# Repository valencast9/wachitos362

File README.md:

# wachitos362
ECE 362 project repository for Team Wachitos.

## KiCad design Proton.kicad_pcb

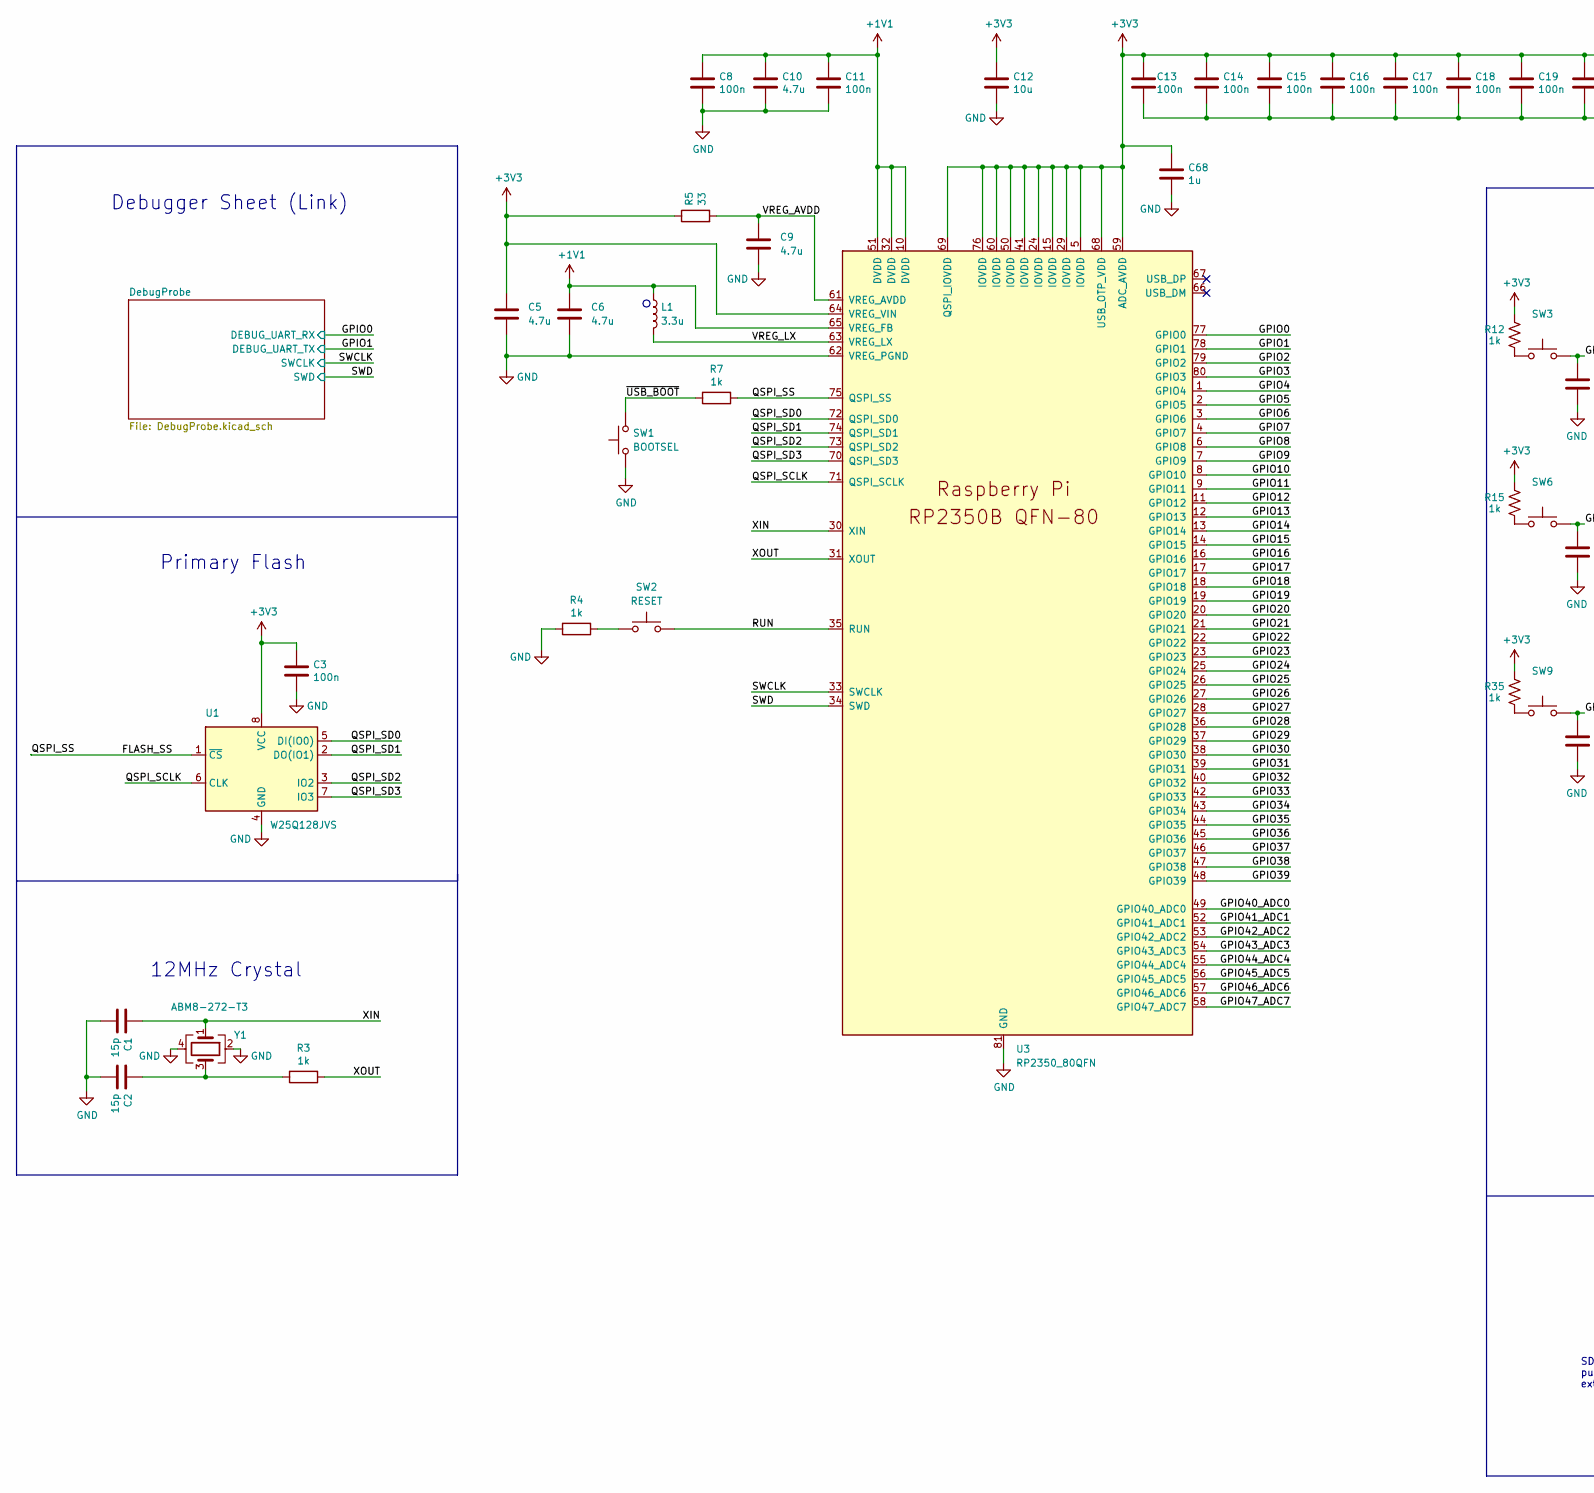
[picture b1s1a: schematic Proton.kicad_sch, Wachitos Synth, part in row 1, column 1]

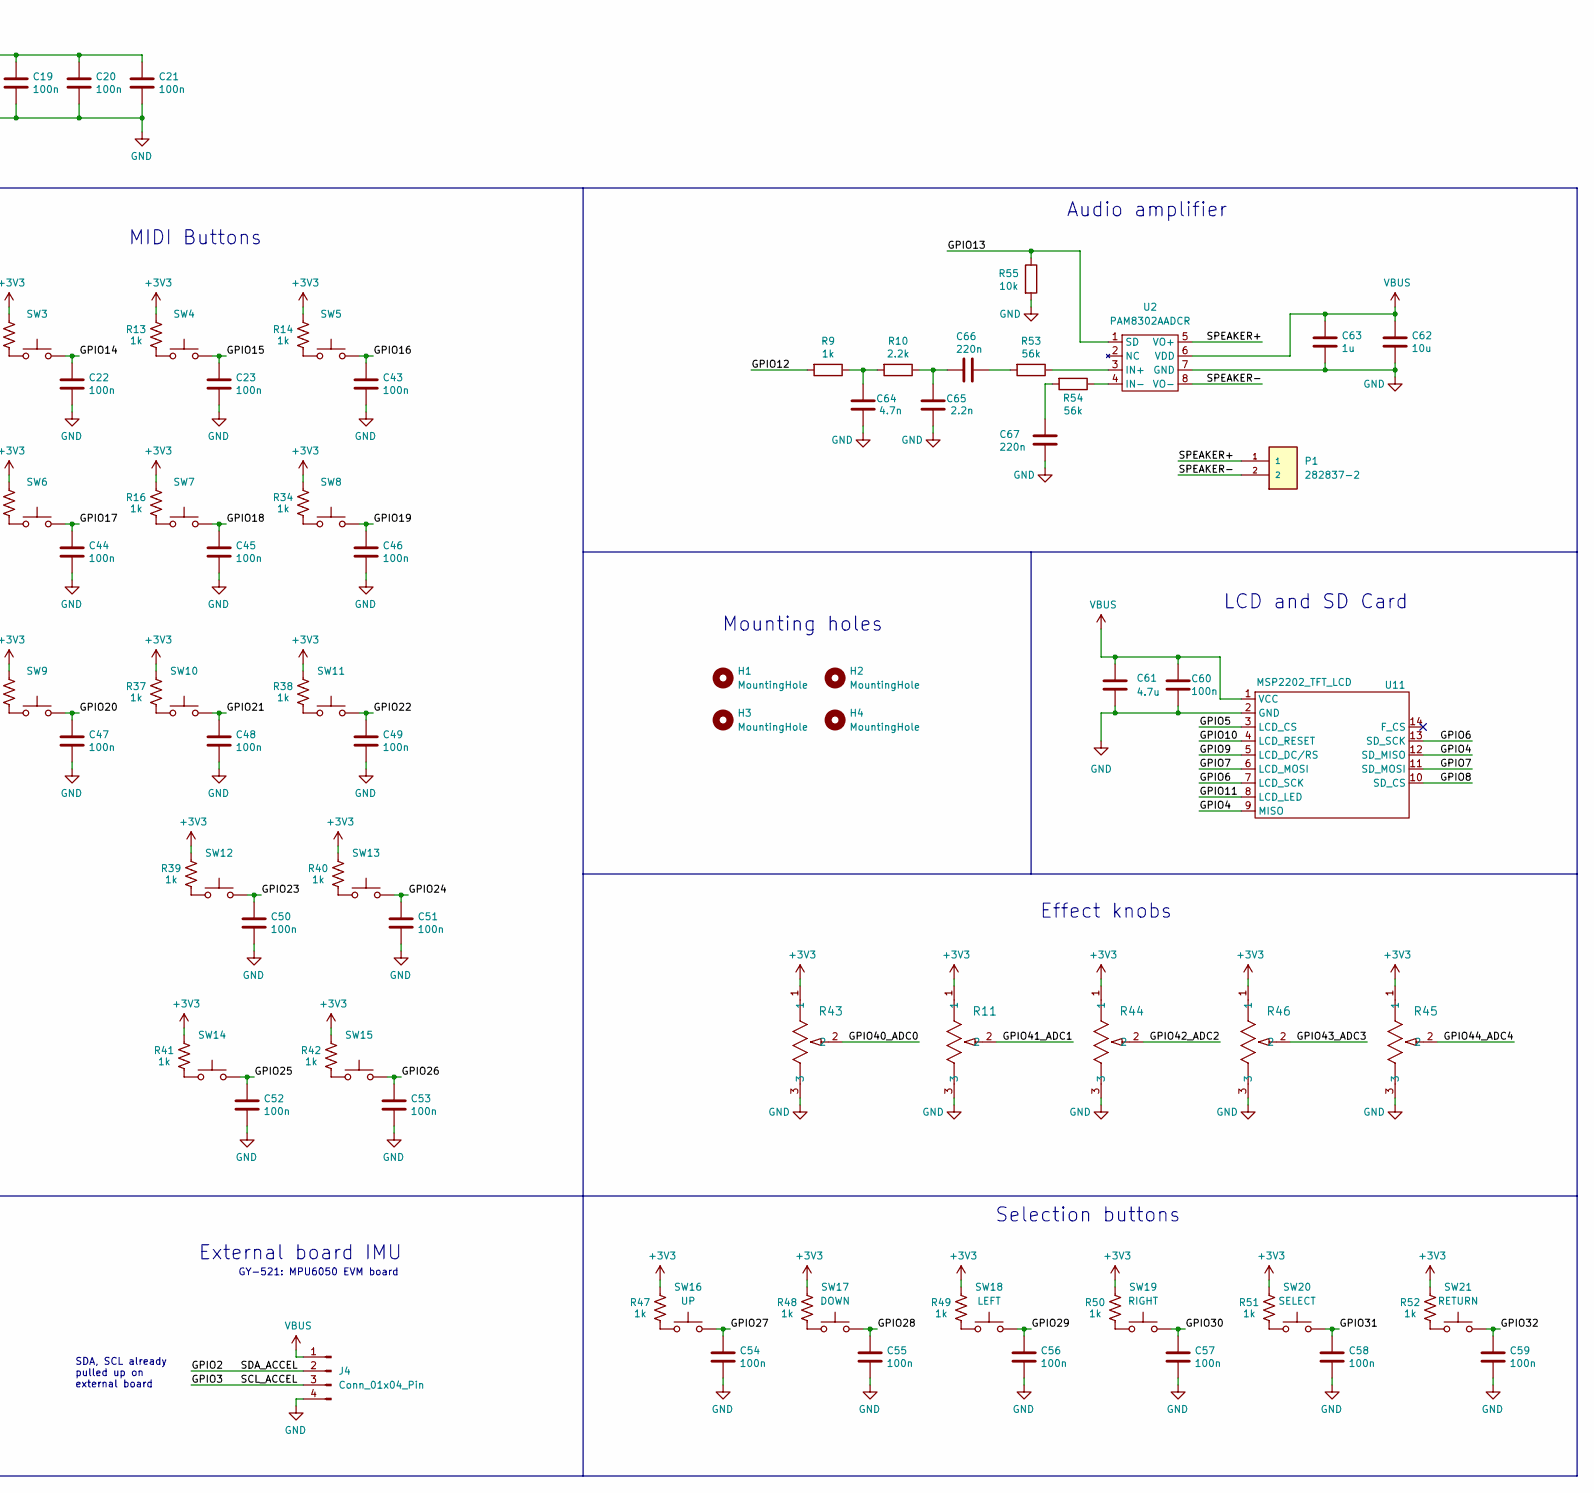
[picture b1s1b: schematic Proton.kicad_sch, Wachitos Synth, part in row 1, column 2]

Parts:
C1, C2: 15p; C_0402_1005Metric; MPN GJM1555C1H150GB01D
C3, C8, C11, C13, C14, C15, C16, C17, C18, C19, C20, C21, C22, C23, C43, C44, C45, C46, C47, C48, C49, C50, C51, C52, C53, C54, C55, C56, C57, C58, C59, C60: 100n; C_0402_1005Metric; MPN CL05B104KP5VPNC
C5, C6, C9, C10, C61: 4.7u; C_0402_1005Metric; MPN CL05A475MP5NRNC
C12, C62: 10u; C_0805_2012Metric; MPN CL21A106KOQNNNE
C63, C68: 1u; C_0402_1005Metric; MPN C1005X6S1C105K050EC
C64: 4.7n; C_0402_1005Metric; MPN CL05B104KP5VPNC
C65: 2.2n; C_0402_1005Metric; MPN CL05B104KP5VPNC
C66, C67: 220n; C_0402_1005Metric; MPN CL05B104KP5VPNC
H1, H2, H3, H4: MountingHole; MountingHole_3.2mm_M3
J4: Conn_01x04_Pin; PinHeader_1x04_P2.54mm_Vertical; MPN PRPC004SACN-RC
L1: 3.3u; L_pol_2016; MPN AOTA-B201610S3R3-101-T
P1: 282837-2; TE_282837-2; PARTREV G3
R3, R4, R7, R9, R12, R13, R14, R15, R16, R34, R35, R37, R38, R39, R40, R41, R42, R47, R48, R49, R50, R51, R52: 1k; R_0402_1005Metric; MPN RC0402JR-071KL
R5: 33; R_0402_1005Metric; MPN RC0402JR-0733RL
R10: 2.2k; R_0402_1005Metric; MPN RC0402JR-071KL
R11, R43, R44, R45, R46: P120PK-Y25BR10K; POT_P120PK-x25_TTE
R53, R54: 56k; R_0402_1005Metric; MPN RC0402JR-071KL
R55: 10k; R_0402_1005Metric; MPN RC0402JR-071KL
SW1: BOOTSEL; SW_SPST_PTS647_Sx38; MPN PTS647SM38SMTR2 LFS
SW2: RESET; SW_SPST_PTS647_Sx38; MPN PTS647SM38SMTR2 LFS
SW3: SW_SPST_PTS647_Sx38; MPN PTS647SM38SMTR2 LFS
SW4, SW5, SW6, SW7, SW8, SW9, SW10, SW11, SW12, SW13, SW14, SW15, SW18: LEFT; SW_SPST_PTS647_Sx38; MPN PTS647SM38SMTR2 LFS
SW16: UP; SW_SPST_PTS647_Sx38; MPN PTS647SM38SMTR2 LFS
SW17: DOWN; SW_SPST_PTS647_Sx38; MPN PTS647SM38SMTR2 LFS
SW19: RIGHT; SW_SPST_PTS647_Sx38; MPN PTS647SM38SMTR2 LFS
SW20: SELECT; SW_SPST_PTS647_Sx38; MPN PTS647SM38SMTR2 LFS
SW21: RETURN; SW_SPST_PTS647_Sx38; MPN PTS647SM38SMTR2 LFS
U1: W25Q128JVS; SOIC-8_5.23x5.23mm_P1.27mm; MPN W25Q128JVSIQ
U2: PAM8302AADCR
U3: RP2350_80QFN; RP2350-QFN-80-1EP_10x10_P0.4mm_EP3.4x3.4mm_ThermalVias; MPN SC1510-A4
U11: MSP2202_TFT_LCD; MSP2202
Y1: ABM8-272-T3; Crystal_SMD_3225-4Pin_3.2x2.5mm; MPN ABM8-272-T3

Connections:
+1V1: C6.1, C8.1, C10.1, C11.1, L1.1, U3.10 (DVDD), U3.32 (DVDD), U3.51 (DVDD), U3.65 (VREG_FB)
+3V3: C3.1, C5.1, C12.1, C13.1, C14.1, C15.1, C16.1, C17.1, C18.1, C19.1, C20.1, C21.1, C68.1, R5.1, R11.1, R12.1, R13.1, R14.1, R15.1, R16.1, R34.1, R35.1, R37.1, R38.1, R39.1, R40.1, R41.1, R42.1, R43.1, R44.1, R45.1, R46.1, R47.1, R48.1, R49.1, R50.1, R51.1, R52.1, U1.8 (VCC), U3.5 (IOVDD), U3.15 (IOVDD), U3.24 (IOVDD), U3.29 (IOVDD), U3.41 (IOVDD), U3.50 (IOVDD), U3.59 (ADC_AVDD), U3.60 (IOVDD), U3.64 (VREG_VIN), U3.68 (USB_OTP_VDD), U3.69 (QSPI_IOVDD), U3.76 (IOVDD); also elsewhere on the board
/FLASH_SS: R7.1, U1.1 (~CS), U3.75 (QSPI_SS)
/GPIO0: U3.77 (GPIO0); also elsewhere on the board
/GPIO1: U3.78 (GPIO1); also elsewhere on the board
/GPIO2: J4.2, U3.79 (GPIO2)
/GPIO3: J4.3, U3.80 (GPIO3)
/GPIO4: U3.1 (GPIO4), U11.9 (MISO), U11.12 (SD_MISO)
/GPIO5: U3.2 (GPIO5), U11.3 (LCD_CS)
/GPIO6: U3.3 (GPIO6), U11.7 (LCD_SCK), U11.13 (SD_SCK)
/GPIO7: U3.4 (GPIO7), U11.6 (LCD_MOSI), U11.11 (SD_MOSI)
/GPIO8: U3.6 (GPIO8), U11.10 (SD_CS)
/GPIO9: U3.7 (GPIO9), U11.5 (LCD_DC/RS)
/GPIO10: U3.8 (GPIO10), U11.4 (LCD_RESET)
/GPIO11: U3.9 (GPIO11), U11.8 (LCD_LED)
/GPIO12: R9.2, U3.11 (GPIO12)
/GPIO13: R55.1, U2.1 (SD), U3.12 (GPIO13)
/GPIO14: C22.1, SW3.2, U3.13 (GPIO14)
/GPIO15: C23.1, SW4.2, U3.14 (GPIO15)
/GPIO16: C43.1, SW5.2, U3.16 (GPIO16)
/GPIO17: C44.1, SW6.2, U3.17 (GPIO17)
/GPIO18: C45.1, SW7.2, U3.18 (GPIO18)
/GPIO19: C46.1, SW8.2, U3.19 (GPIO19)
/GPIO20: C47.1, SW9.2, U3.20 (GPIO20)
/GPIO21: C48.1, SW10.2, U3.21 (GPIO21)
/GPIO22: C49.1, SW11.2, U3.22 (GPIO22)
/GPIO23: C50.1, SW12.2, U3.23 (GPIO23)
/GPIO24: C51.1, SW13.2, U3.25 (GPIO24)
/GPIO25: C52.1, SW14.2, U3.26 (GPIO25)
/GPIO26: C53.1, SW15.2, U3.27 (GPIO26)
/GPIO27: C54.1, SW16.2, U3.28 (GPIO27)
/GPIO28: C55.1, SW17.2, U3.36 (GPIO28)
/GPIO29: C56.1, SW18.2, U3.37 (GPIO29)
/GPIO30: C57.1, SW19.2, U3.38 (GPIO30)
/GPIO31: C58.1, SW20.2, U3.39 (GPIO31)
/GPIO32: C59.1, SW21.2, U3.40 (GPIO32)
/GPIO33: U3.42 (GPIO33)
/GPIO34: U3.43 (GPIO34)
/GPIO35: U3.44 (GPIO35)
/GPIO36: U3.45 (GPIO36)
/GPIO37: U3.46 (GPIO37)
/GPIO38: U3.47 (GPIO38)
/GPIO39: U3.48 (GPIO39)
/GPIO40_ADC0: R43.2, U3.49 (GPIO40_ADC0)
/GPIO41_ADC1: R11.2, U3.52 (GPIO41_ADC1)
/GPIO42_ADC2: R44.2, U3.53 (GPIO42_ADC2)
/GPIO43_ADC3: R46.2, U3.54 (GPIO43_ADC3)
/GPIO44_ADC4: R45.2, U3.55 (GPIO44_ADC4)
/GPIO45_ADC5: U3.56 (GPIO45_ADC5)
/GPIO46_ADC6: U3.57 (GPIO46_ADC6)
/GPIO47_ADC7: U3.58 (GPIO47_ADC7)
/QSPI_SCLK: U1.6 (CLK), U3.71 (QSPI_SCLK)
/QSPI_SD0: U1.5 (DI(IO0)), U3.72 (QSPI_SD0)
/QSPI_SD1: U1.2 (DO(IO1)), U3.74 (QSPI_SD1)
/QSPI_SD2: U1.3 (IO2), U3.73 (QSPI_SD2)
/QSPI_SD3: U1.7 (IO3), U3.70 (QSPI_SD3)
/RUN: SW2.2, U3.35 (RUN)
/SPEAKER+: P1.1, U2.5 (VO+)
/SPEAKER-: P1.2, U2.8 (VO-)
/VREG_AVDD: C9.1, R5.2, U3.61 (VREG_AVDD)
/VREG_LX: L1.2, U3.63 (VREG_LX)
/XIN: C1.1, U3.30 (XIN), Y1.1
/XOUT: R3.1, U3.31 (XOUT)
/~USB_BOOT: R7.2, SW1.2
GND: C1.2, C2.2, C3.2, C5.2, C6.2, C8.2, C9.2, C10.2, C11.2, C12.2, C13.2, C14.2, C15.2, C16.2, C17.2, C18.2, C19.2, C20.2, C21.2, C22.2, C23.2, C43.2, C44.2, C45.2, C46.2, C47.2, C48.2, C49.2, C50.2, C51.2, C52.2, C53.2, C54.2, C55.2, C56.2, C57.2, C58.2, C59.2, C60.2, C61.2, C62.2, C63.2, C64.2, C65.2, C67.1, C68.2, J4.4, R4.2, R11.3, R43.3, R44.3, R45.3, R46.3, R55.2, SW1.1, U1.4 (GND), U2.7 (GND), U3.62 (VREG_PGND), U3.81 (GND), U11.2 (GND), Y1.2, Y1.4; also elsewhere on the board
unnamed: C2.1, R3.2, Y1.3
unnamed: C64.1, R9.1, R10.2
unnamed: C65.1, C66.1, R10.1
unnamed: C66.2, R53.2
unnamed: C67.2, R54.2
unnamed: R4.1, SW2.1
unnamed: R12.2, SW3.1
unnamed: R13.2, SW4.1
unnamed: R14.2, SW5.1
unnamed: R15.2, SW6.1
unnamed: R16.2, SW7.1
unnamed: R34.2, SW8.1
unnamed: R35.2, SW9.1
unnamed: R37.2, SW10.1
unnamed: R38.2, SW11.1
unnamed: R39.2, SW12.1
unnamed: R40.2, SW13.1
unnamed: R41.2, SW14.1
unnamed: R42.2, SW15.1
unnamed: R47.2, SW16.1
unnamed: R48.2, SW17.1
unnamed: R49.2, SW18.1
unnamed: R50.2, SW19.1
unnamed: R51.2, SW20.1
unnamed: R52.2, SW21.1
unnamed: R53.1, U2.3 (IN+)
unnamed: R54.1, U2.4 (IN-)
PSWCLK: U3.33 (SWCLK); also elsewhere on the board
PSWD: U3.34 (SWD); also elsewhere on the board
VBUS: C60.1, C61.1, C62.1, C63.1, J4.1, U2.6 (VDD), U11.1 (VCC); also elsewhere on the board

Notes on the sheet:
Effect knobs
Selection buttons
LCD and SD Card
12MHz Crystal
SDA, SCL already pulled up on external board
Audio amplifier
Primary Flash
Mounting holes
GY-521: MPU6050 EVM board
Debugger Sheet (Link)
MIDI Buttons
External board IMU

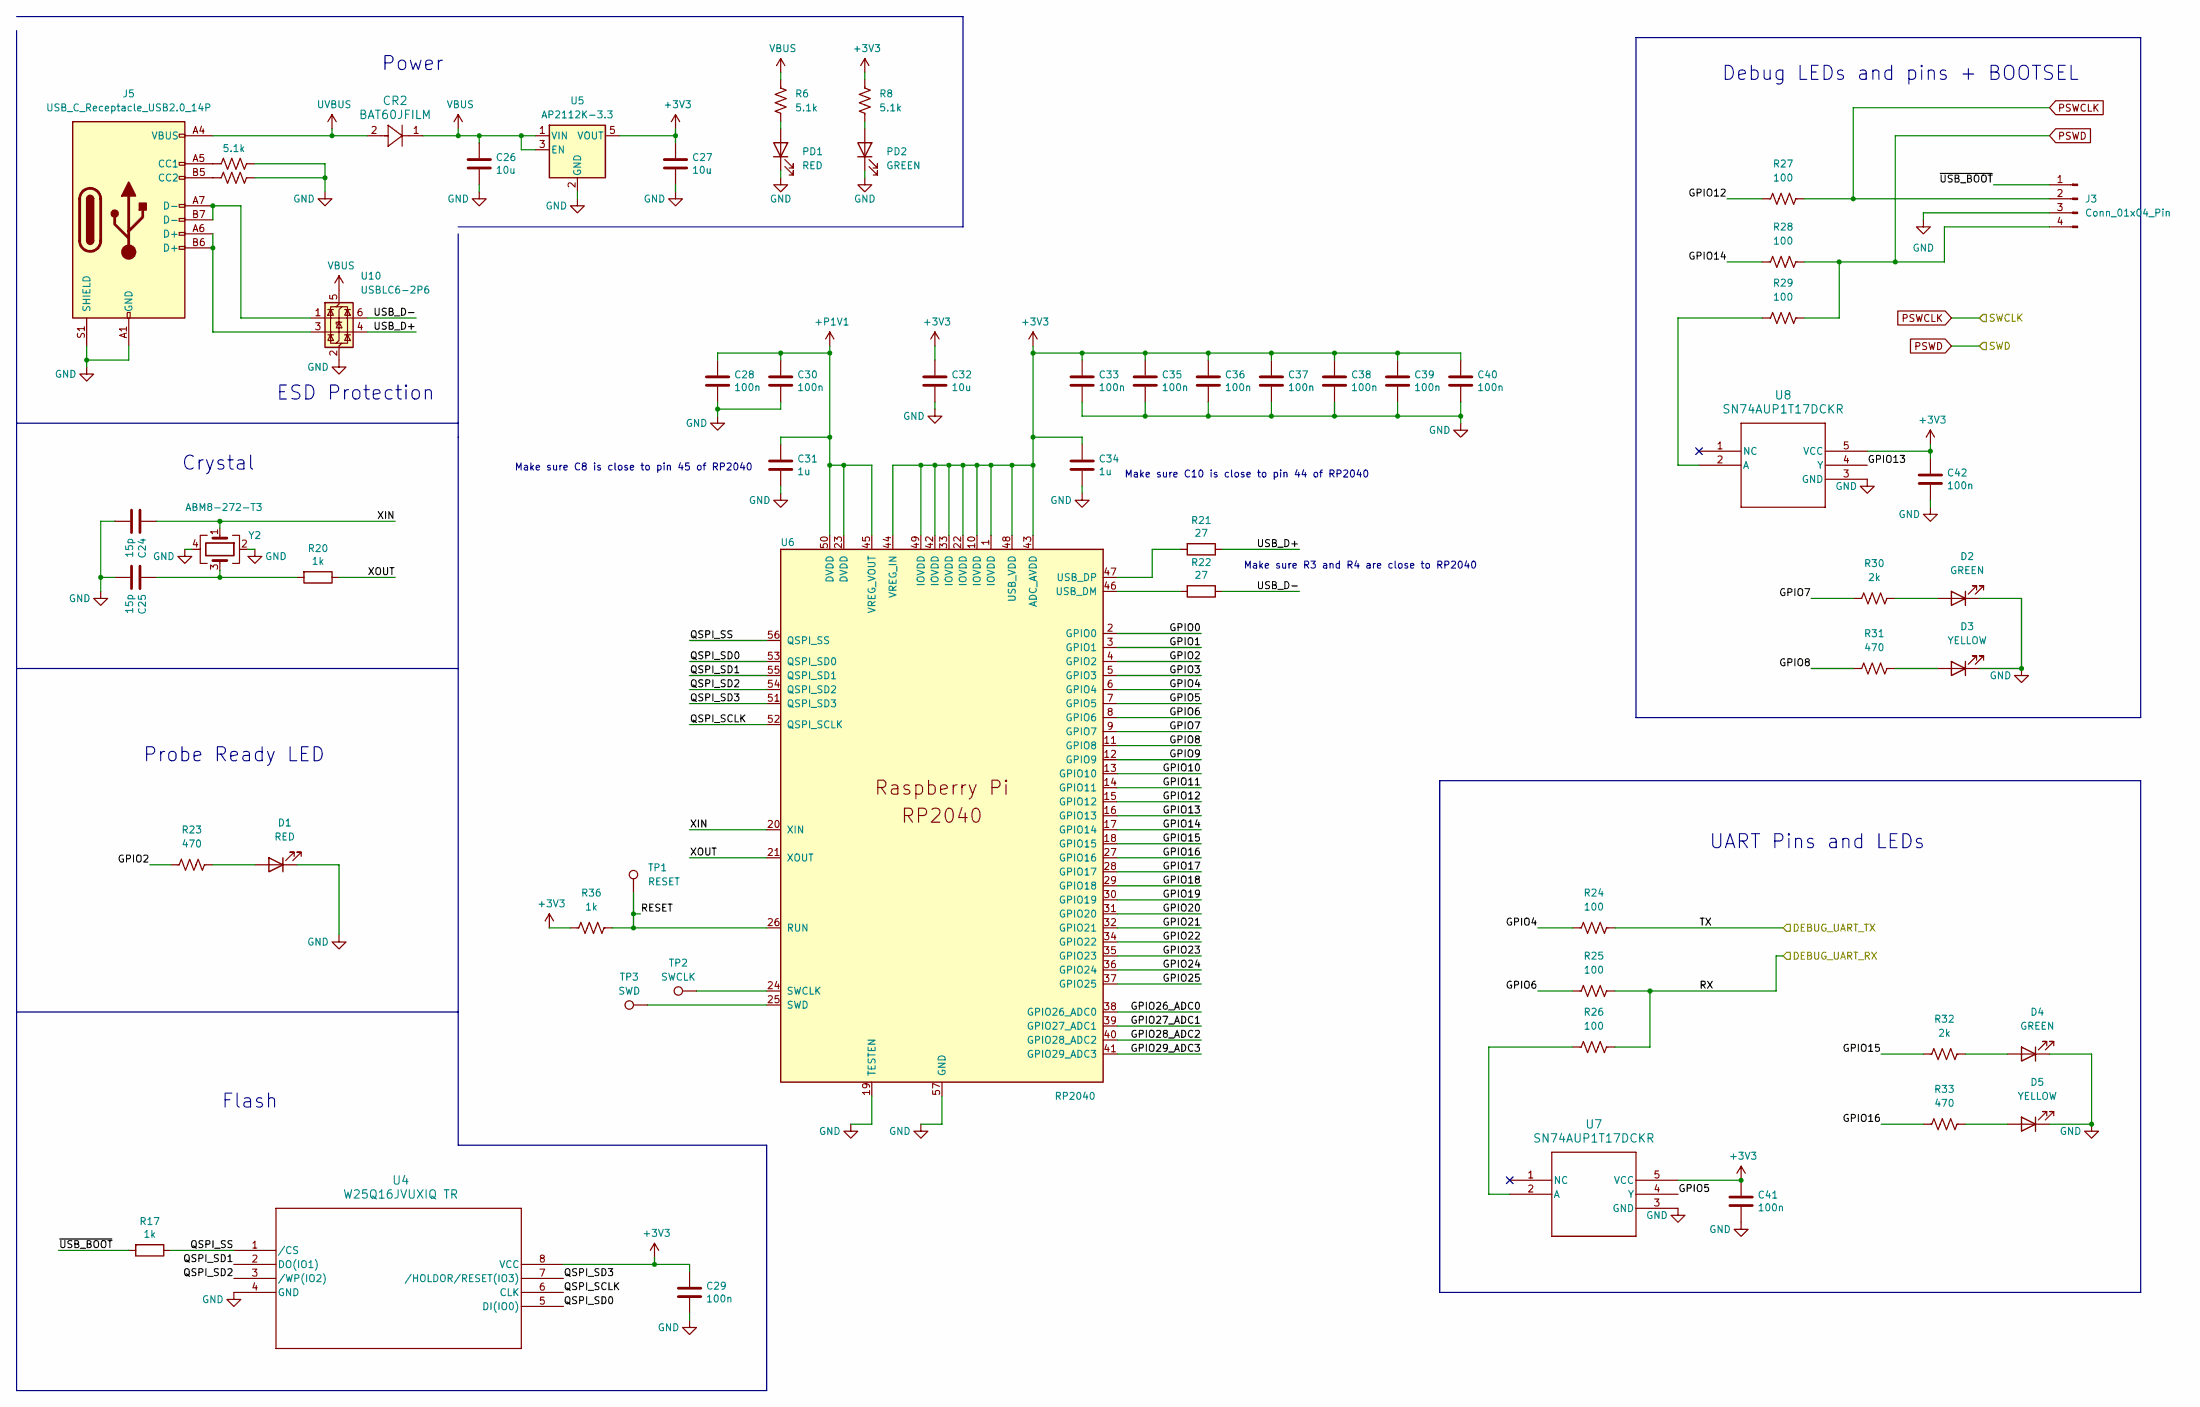
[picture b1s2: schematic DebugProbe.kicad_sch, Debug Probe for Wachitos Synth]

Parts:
C24, C25: 15p; C_0402_1005Metric; MPN GJM1555C1H150GB01D
C26: 10u; C_0805_2012Metric; MPN CL21A106KOQNNNE
C27, C32: 10u; C_0603_1608Metric; MPN 0603X106M100CT
C28, C29, C30, C33, C35, C36, C37, C38, C39, C40, C41, C42: 100n; C_0402_1005Metric; MPN CL05B104KP5VPNC
C31, C34: 1u; C_0402_1005Metric; MPN C1005X6S1C105K050EC
CR2: BAT60JFILM; CR_60JFILM_STM; MPN BAT60A-TR
D1: RED; D_0402_1005Metric; MPN QBLP595-R
D2, D4: GREEN; D_0402_1005Metric; MPN IN-S42BT5G
D3, D5: YELLOW; D_0402_1005Metric; MPN QBLP595-Y5
J3: Conn_01x04_Pin; PinHeader_1x04_P2.54mm_Vertical; MPN PRPC004SACN-RC
J5: USB_C_Receptacle_USB2.0_14P; USB_C_Receptacle_G-Switch_GT-USB-7010ASV; MPN UJ20-C-H-G-SMT-1-P16-TR
PD1: RED; LED_0805_2012Metric; MPN LS R976-NR-1-0-20-R18
PD2: GREEN; LED_0805_2012Metric; MPN LG R971-KN-1-0-20-R18
R6, R8, R18, R19: 5.1k; R_0402_1005Metric; MPN RK73H1ETTP5101F
R17, R20, R36: 1k; R_0402_1005Metric; MPN RC0402JR-071KL
R21, R22: 27; R_0402_1005Metric; MPN RC0402JR-0727RL
R23, R31, R33: 470; R_0402_1005Metric; MPN BLM15BB470SN1D
R24, R25, R26, R27, R28, R29: 100; R_0402_1005Metric; MPN RC0402FR-07100RL
R30, R32: 2k; R_0402_1005Metric; MPN RC0402FR-072KL
TP1: RESET; TestPoint_Pad_D1.0mm; MPN PTS647SM38SMTR2 LFS
TP2: SWCLK; TestPoint_Pad_D1.0mm
TP3: SWD; TestPoint_Pad_D1.0mm
U4: W25Q16JVUXIQ TR; USON-8_UX_2x3x0p6_WIN; MPN MX25V1635FZUI
U5: AP2112K-3.3; SOT-23-5; MPN AP2112K-3.3TRG1
U6: RP2040; RP2040-QFN-56; MPN MAKER-PI-RP2040
U7, U8: SN74AUP1T17DCKR; DCK5; MPN SN74LVC1G17DCKR
U10: USBLC6-2P6; SOT-666; MPN USBLC6-2P6
Y2: ABM8-272-T3; Crystal_SMD_3225-4Pin_3.2x2.5mm; MPN ABM8-272-T3

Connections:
+3V3: C27.1, C29.1, C32.1, C33.1, C34.1, C35.1, C36.1, C37.1, C38.1, C39.1, C40.1, C41.1, C42.1, R8.1, R36.1, U4.8 (VCC), U5.5 (VOUT), U6.1 (IOVDD), U6.10 (IOVDD), U6.22 (IOVDD), U6.33 (IOVDD), U6.42 (IOVDD), U6.43 (ADC_AVDD), U6.44 (VREG_IN), U6.48 (USB_VDD), U6.49 (IOVDD), U7.5 (VCC), U8.5 (VCC); also elsewhere on the board
+P1V1: C28.1, C30.1, C31.1, U6.23 (DVDD), U6.45 (VREG_VOUT), U6.50 (DVDD)
/DebugProbe/GPIO0: U6.2 (GPIO0)
/DebugProbe/GPIO1: U6.3 (GPIO1)
/DebugProbe/GPIO2: R23.1, U6.4 (GPIO2)
/DebugProbe/GPIO3: U6.5 (GPIO3)
/DebugProbe/GPIO4: R24.1, U6.6 (GPIO4)
/DebugProbe/GPIO5: U6.7 (GPIO5), U7.4 (Y)
/DebugProbe/GPIO6: R25.1, U6.8 (GPIO6)
/DebugProbe/GPIO7: R30.1, U6.9 (GPIO7)
/DebugProbe/GPIO8: R31.1, U6.11 (GPIO8)
/DebugProbe/GPIO9: U6.12 (GPIO9)
/DebugProbe/GPIO10: U6.13 (GPIO10)
/DebugProbe/GPIO11: U6.14 (GPIO11)
/DebugProbe/GPIO12: R27.1, U6.15 (GPIO12)
/DebugProbe/GPIO13: U6.16 (GPIO13), U8.4 (Y)
/DebugProbe/GPIO14: R28.1, U6.17 (GPIO14)
/DebugProbe/GPIO15: R32.1, U6.18 (GPIO15)
/DebugProbe/GPIO16: R33.1, U6.27 (GPIO16)
/DebugProbe/GPIO17: U6.28 (GPIO17)
/DebugProbe/GPIO18: U6.29 (GPIO18)
/DebugProbe/GPIO19: U6.30 (GPIO19)
/DebugProbe/GPIO20: U6.31 (GPIO20)
/DebugProbe/GPIO21: U6.32 (GPIO21)
/DebugProbe/GPIO22: U6.34 (GPIO22)
/DebugProbe/GPIO23: U6.35 (GPIO23)
/DebugProbe/GPIO24: U6.36 (GPIO24)
/DebugProbe/GPIO25: U6.37 (GPIO25)
/DebugProbe/GPIO26_ADC0: U6.38 (GPIO26_ADC0)
/DebugProbe/GPIO27_ADC1: U6.39 (GPIO27_ADC1)
/DebugProbe/GPIO28_ADC2: U6.40 (GPIO28_ADC2)
/DebugProbe/GPIO29_ADC3: U6.41 (GPIO29_ADC3)
/DebugProbe/QSPI_SCLK: U4.6 (CLK), U6.52 (QSPI_SCLK)
/DebugProbe/QSPI_SD0: U4.5 (DI(IO0)), U6.53 (QSPI_SD0)
/DebugProbe/QSPI_SD1: U4.2 (DO(IO1)), U6.55 (QSPI_SD1)
/DebugProbe/QSPI_SD2: U4.3 (/WP(IO2)), U6.54 (QSPI_SD2)
/DebugProbe/QSPI_SD3: U4.7 (/HOLDOR/RESET(IO3)), U6.51 (QSPI_SD3)
/DebugProbe/QSPI_SS: R17.1, U4.1 (/CS), U6.56 (QSPI_SS); also elsewhere on the board
/DebugProbe/RESET: R36.2, TP1.1 (1_1), U6.26 (RUN)
/DebugProbe/USB_D+: R21.1, U10.4 (I/O2)
/DebugProbe/USB_D-: R22.1, U10.6 (I/O1)
/DebugProbe/XIN: C24.1, U6.20 (XIN), Y2.1
/DebugProbe/XOUT: R20.1, U6.21 (XOUT)
/DebugProbe/~USB_BOOT: J3.1, R17.2; also elsewhere on the board
/GPIO0: R25.2, R26.2; also elsewhere on the board
/GPIO1: R24.2; also elsewhere on the board
GND: C24.2, C25.2, C26.2, C27.2, C28.2, C29.2, C30.2, C31.2, C32.2, C33.2, C34.2, C35.2, C36.2, C37.2, C38.2, C39.2, C40.2, C41.2, C42.2, D1.1 (K), D2.1 (K), D3.1 (K), D4.1 (K), D5.1 (K), J3.3, J5.A1 (GND), J5.A12 (GND), J5.B1 (GND), J5.B12 (GND), J5.S1 (SHIELD), PD1.1 (K), PD2.1 (K), R18.2, R19.2, U4.4 (GND), U5.2 (GND), U6.19 (TESTEN), U6.57 (GND), U7.3 (GND), U8.3 (GND), U10.2 (GND), Y2.2, Y2.4; also elsewhere on the board
unnamed: C25.1, R20.2, Y2.3
unnamed: D1.2 (A), R23.2
unnamed: D2.2 (A), R30.2
unnamed: D3.2 (A), R31.2
unnamed: D4.2 (A), R32.2
unnamed: D5.2 (A), R33.2
unnamed: J5.A5 (CC1), R18.1
unnamed: J5.B5 (CC2), R19.1
unnamed: J5.A6 (D+), J5.B6 (D+), U10.3 (I/O2)
unnamed: J5.A7 (D-), J5.B7 (D-), U10.1 (I/O1)
unnamed: PD1.2 (A), R6.2
unnamed: PD2.2 (A), R8.2
unnamed: TP2.1 (1_1), U6.24 (SWCLK)
unnamed: TP3.1 (1_1), U6.25 (SWD)
unnamed: R22.2, U6.46 (USB_DM)
unnamed: R21.2, U6.47 (USB_DP)
unnamed: R26.1, U7.2 (A)
unnamed: R29.1, U8.2 (A)
PSWCLK: J3.2, R27.2; also elsewhere on the board
PSWD: J3.4, R28.2, R29.2; also elsewhere on the board
UVBUS: CR2.2, J5.A4 (VBUS), J5.A9 (VBUS), J5.B4 (VBUS), J5.B9 (VBUS)
VBUS: C26.1, CR2.1, R6.1, U5.1 (VIN), U5.3 (EN), U10.5 (VBUS); also elsewhere on the board

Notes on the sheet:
ESD Protection
Probe Ready LED
Crystal
Power
Make sure C8 is close to pin 45 of RP2040
Make sure C10 is close to pin 44 of RP2040
UART Pins and LEDs
Debug LEDs and pins + BOOTSEL
Make sure R3 and R4 are close to RP2040
Flash

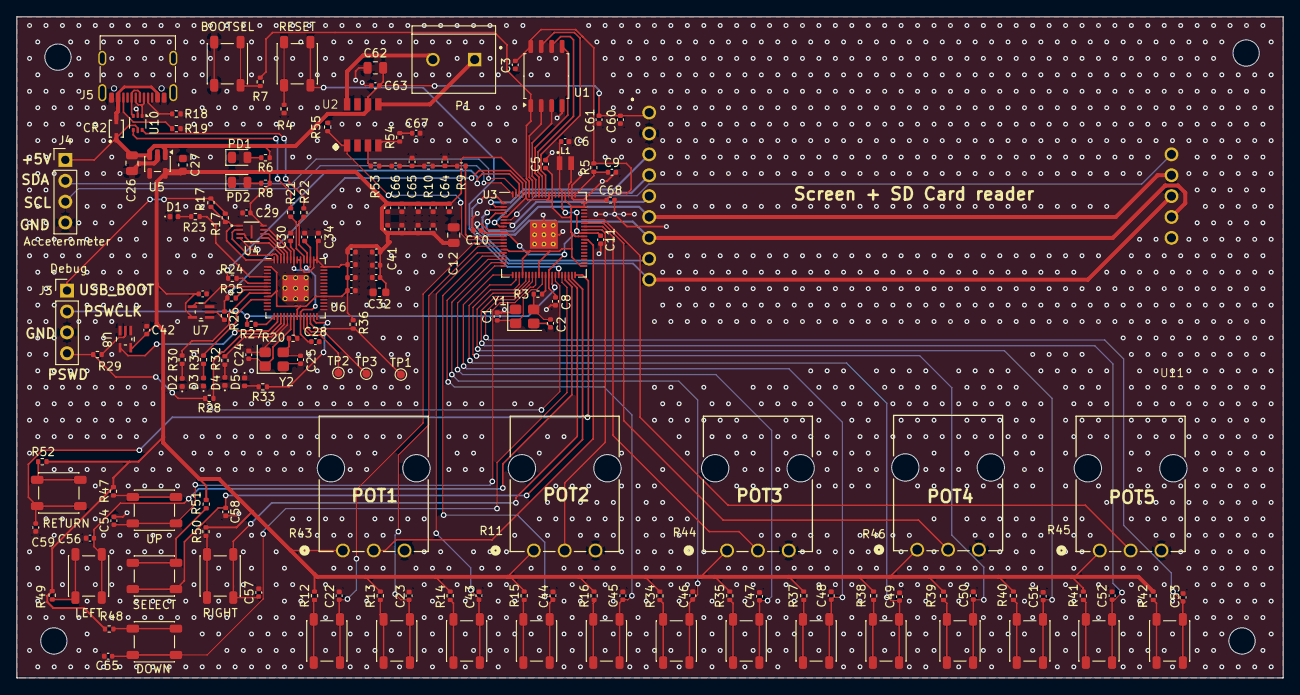
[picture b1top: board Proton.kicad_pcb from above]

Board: 4 copper layers, 154.0 x 80.4 mm, 173 parts (0 on the bottom side), 128 nets.

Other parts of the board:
R17#2: 1k; R_0402_1005Metric

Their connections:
/DebugProbe/QSPI_SS: R17#2.1; also elsewhere on the board
/DebugProbe/~USB_BOOT: R17#2.2; also elsewhere on the board

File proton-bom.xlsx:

Designator | Value | Footprint | MPN | Manufacturer
C1 | 15p | C_0402_1005Metric | GJM1555C1H150GB01D | Murata
C10 | 4.7u | C_0402_1005Metric | JMK105BBJ475MV-F | TAIYO YUDEN
C11 | 100n | C_0402_1005Metric | LMK105BJ104KV-F | TAIYO YUDEN
C12 | 10u | C_0805_2012Metric | GRM21BR61C106KE15K | Murata
C13 | 100n | C_0402_1005Metric | LMK105BJ104KV-F | TAIYO YUDEN
C14 | 100n | C_0402_1005Metric | LMK105BJ104KV-F | TAIYO YUDEN
C15 | 100n | C_0402_1005Metric | LMK105BJ104KV-F | TAIYO YUDEN
C16 | 100n | C_0402_1005Metric | LMK105BJ104KV-F | TAIYO YUDEN
C17 | 100n | C_0402_1005Metric | LMK105BJ104KV-F | TAIYO YUDEN
C18 | 100n | C_0402_1005Metric | LMK105BJ104KV-F | TAIYO YUDEN
C19 | 100n | C_0402_1005Metric | LMK105BJ104KV-F | TAIYO YUDEN
C2 | 15p | C_0402_1005Metric | GJM1555C1H150GB01D | Murata
C20 | 100n | C_0402_1005Metric | LMK105BJ104KV-F | TAIYO YUDEN
C21 | 100n | C_0402_1005Metric | LMK105BJ104KV-F | TAIYO YUDEN
C22 | 100n | C_0402_1005Metric | LMK105BJ104KV-F | TAIYO YUDEN
C23 | 100n | C_0402_1005Metric | LMK105BJ104KV-F | TAIYO YUDEN
C24 | 15p | C_0402_1005Metric | GJM1555C1H150GB01D | Murata
C25 | 15p | C_0402_1005Metric | GJM1555C1H150GB01D | Murata
C26 | 10u | C_0805_2012Metric | GRM21BR61C106KE15K | Murata
C27 | 10u | C_0603_1608Metric | JMK107BJ106MA-T | TAIYO YUDEN
C28 | 100n | C_0402_1005Metric | LMK105BJ104KV-F | TAIYO YUDEN
C29 | 100n | C_0402_1005Metric | LMK105BJ104KV-F | TAIYO YUDEN
C3 | 100n | C_0402_1005Metric | LMK105BJ104KV-F | TAIYO YUDEN
C30 | 100n | C_0402_1005Metric | LMK105BJ104KV-F | TAIYO YUDEN
C31 | 1u | C_0402_1005Metric | JMK105BJ105KV-F | TAIYO YUDEN
C32 | 10u | C_0603_1608Metric | JMK107BJ106MA-T | TAIYO YUDEN
C33 | 100n | C_0402_1005Metric | LMK105BJ104KV-F | TAIYO YUDEN
C34 | 1u | C_0402_1005Metric | JMK105BJ105KV-F | TAIYO YUDEN
C35 | 100n | C_0402_1005Metric | LMK105BJ104KV-F | TAIYO YUDEN
C36 | 100n | C_0402_1005Metric | LMK105BJ104KV-F | TAIYO YUDEN
C37 | 100n | C_0402_1005Metric | LMK105BJ104KV-F | TAIYO YUDEN
C38 | 100n | C_0402_1005Metric | LMK105BJ104KV-F | TAIYO YUDEN
C39 | 100n | C_0402_1005Metric | LMK105BJ104KV-F | TAIYO YUDEN
C4 | 10u | C_0805_2012Metric | GRM21BR61C106KE15K | Murata
C40 | 100n | C_0402_1005Metric | LMK105BJ104KV-F | TAIYO YUDEN
C41 | 100n | C_0402_1005Metric | LMK105BJ104KV-F | TAIYO YUDEN
C42 | 100n | C_0402_1005Metric | LMK105BJ104KV-F | TAIYO YUDEN
C5 | 4.7u | C_0402_1005Metric_small_pads | JMK105BBJ475MV-F | TAIYO YUDEN
C6 | 4.7u | C_0402_1005Metric_small_pads | JMK105BBJ475MV-F | TAIYO YUDEN
C7 | 10u | C_0805_2012Metric | GRM21BR61C106KE15K | Murata
C8 | 100n | C_0402_1005Metric | LMK105BJ104KV-F | TAIYO YUDEN
C9 | 4.7u | C_0402_1005Metric | JMK105BBJ475MV-F | TAIYO YUDEN
CR1 | BAT60JFILM | CR_60JFILM_STM | BAT60JFILM | STMicroelectronics
CR2 | BAT60JFILM | CR_60JFILM_STM | BAT60JFILM | STMicroelectronics
D1 | RED | D_0402_1005Metric | LTST-C281KRKT | Lite-On
D2 | GREEN | D_0402_1005Metric | XZVG68W-2 | SunLED
D3 | YELLOW | D_0402_1005Metric | QBLP595-Y | QT Brightek
D4 | GREEN | D_0402_1005Metric | XZVG68W-2 | SunLED
D5 | YELLOW | D_0402_1005Metric | QBLP595-Y | QT Brightek
J1 | USB_C_Receptacle_USB2.0_14P | USB_C_Receptacle_G-Switch_GT-USB-7010ASV | USB4056-03-A | Global Connector Technology
J2 | Conn_01x28_Pin | PinHeader_1x28_P2.54mm_Vertical | PRPC028SACN-RC | Sullins
J3 | Conn_01x04_Pin | PinHeader_1x04_P2.54mm_Vertical | PRPC004SACN-RC | Sullins
J4 | Conn_01x28_Pin | PinHeader_1x28_P2.54mm_Vertical | PRPC028SACN-RC | Sullins
J5 | USB_C_Receptacle_USB2.0_14P | USB_C_Receptacle_G-Switch_GT-USB-7010ASV | USB4056-03-A | Global Connector Technology
J6 | Conn_01x03_Socket | PinSocket_1x03_P2.54mm_Vertical | 61300311121 | Wurth Elektronik
J7 | UART-PINS | PinHeader_1x03_P2.54mm_Vertical | PRPC003SACN-RC | Sullins
J8 | Conn_01x03_Socket | PinSocket_1x03_P2.54mm_Vertical | 61300311121 | Wurth Elektronik
L1 | 3.3u | L_pol_2016 | AOTA-B201610S3R3-101-T | Abracon
PD1 | RED | LED_0805_2012Metric | LTST-C170KRKT | Diodes Inc.
PD2 | GREEN | LED_0805_2012Metric | LTST-C171KGKT | Diodes Inc.
R1 | 5.1k | R_0402_1005Metric | RC0402JR-135K1L | Yageo Group
R10 | 27 | R_0402_1005Metric | RC0402JR-0727RL | Yageo Group
R11 | 3k | R_0402_1005Metric | RC0402JR-073KL | Yageo Group
R12 | 1k | R_0402_1005Metric | RC0402JR-071KL | Yageo Group
R13 | 2k | R_0402_1005Metric | RC0402JR-072KL | Yageo Group
R14 | 1k | R_0402_1005Metric | RC0402JR-071KL | Yageo Group
R15 | 1k | R_0402_1005Metric | RC0402JR-071KL | Yageo Group
R16 | 510 | R_0402_1005Metric | RC0402JR-07510RL | Yageo Group
R17 | 1k | R_0402_1005Metric | RC0402JR-071KL | Yageo Group
R18 | 5.1k | R_0402_1005Metric | RC0402JR-135K1L | Yageo Group
R19 | 5.1k | R_0402_1005Metric | RC0402JR-135K1L | Yageo Group
R2 | 5.1k | R_0402_1005Metric | RC0402JR-135K1L | Yageo Group
R20 | 1k | R_0402_1005Metric | RC0402JR-071KL | Yageo Group
R21 | 27 | R_0402_1005Metric | RC0402JR-0727RL | Yageo Group
R22 | 27 | R_0402_1005Metric | RC0402JR-0727RL | Yageo Group
R23 | 470 | R_0402_1005Metric | RC0402JR-074K7L | Yageo Group
R24 | 100 | R_0402_1005Metric | RC0402JR-07100RL | Yageo Group
R25 | 100 | R_0402_1005Metric | RC0402JR-07100RL | Yageo Group
R26 | 100 | R_0402_1005Metric | RC0402JR-07100RL | Yageo Group
R27 | 100 | R_0402_1005Metric | RC0402JR-07100RL | Yageo Group
R28 | 100 | R_0402_1005Metric | RC0402JR-07100RL | Yageo Group
R29 | 100 | R_0402_1005Metric | RC0402JR-07100RL | Yageo Group
R3 | 1k | R_0402_1005Metric | RC0402JR-071KL | Yageo Group
R30 | 2k | R_0402_1005Metric | RC0402JR-072KL | Yageo Group
R31 | 470 | R_0402_1005Metric | RC0402JR-074K7L | Yageo Group
R32 | 2k | R_0402_1005Metric | RC0402JR-072KL | Yageo Group
R33 | 470 | R_0402_1005Metric | RC0402JR-074K7L | Yageo Group
R36 | 1k | R_0402_1005Metric | RC0402JR-071KL | Yageo Group
R4 | 1k | R_0402_1005Metric | RC0402JR-071KL | Yageo Group
R5 | 33 | R_0402_1005Metric | RC0402JR-0733RL | Yageo Group
R6 | 5.1k | R_0402_1005Metric | RC0402JR-135K1L | Yageo Group
R7 | 1k | R_0402_1005Metric | RC0402JR-071KL | Yageo Group
R8 | 5.1k | R_0402_1005Metric | RC0402JR-135K1L | Yageo Group
R9 | 27 | R_0402_1005Metric | RC0402JR-0727RL | Yageo Group
SW1 | BOOTSEL | SW_SPST_PTS647_Sx38 | PTS647SM38SMTR2LFS | C&K Components
SW2 | RESET | SW_SPST_PTS647_Sx38 | PTS647SM38SMTR2LFS | C&K Components
SW3 | LEFT | SW_SPST_PTS647_Sx38 | PTS647SM38SMTR2LFS | C&K Components
SW4 | RIGHT | SW_SPST_PTS647_Sx38 | PTS647SM38SMTR2LFS | C&K Components
U1 | W25Q128JVS | SOIC-8_5.23x5.23mm_P1.27mm | W25Q128JVSIQ | Winbond
U10 | USBLC6-2P6 | SOT-666 | USBLC6-2P6 | STMicroelectronics
U2 | NCP1117-3.3_SOT223 | SOT-223-3_TabPin2 | NCP1117ST33T3G | onsemi
U3 | RP2350_80QFN | RP2350-QFN-80-1EP_10x10_P0.4mm_EP3.4x3.4mm_ThermalVias | SC1510-A4 | Raspberry Pi
U4 | W25Q16JVUXIQ TR | USON-8_UX_2x3x0p6_WIN | W25Q16JVUXIQ TR | Winbond
U5 | AP2112K-3.3 | SOT-23-5 | AP2112K-3.3TRG1 | Diodes Inc.
U6 | RP2040 | RP2040-QFN-56 | RP2040 | Raspberry Pi
U7 | SN74AUP1T17DCKR | DCK5 | SN74AUP1T17DCKR | Texas Instruments
U8 | SN74AUP1T17DCKR | DCK5 | SN74AUP1T17DCKR | Texas Instruments
U9 | USBLC6-2P6 | SOT-666 | USBLC6-2P6 | STMicroelectronics
UD1 | RED | LED_0805_2012Metric | LTST-C170KRKT | Diodes Inc.
UD2 | YELLOW | LED_0805_2012Metric | LTST-C170KSKT | Diodes Inc.
UD3 | GREEN | LED_0805_2012Metric | LTST-C171KGKT | Diodes Inc.
UD4 | BLUE | LED_0805_2012Metric | 150080BS75000 | Wurth Elektronik
Y1 | ABM8-272-T3 | Crystal_SMD_3225-4Pin_3.2x2.5mm | ABM8-272-T3 | Abracon
Y2 | ABM8-272-T3 | Crystal_SMD_3225-4Pin_3.2x2.5mm | ABM8-272-T3 | Abracon
